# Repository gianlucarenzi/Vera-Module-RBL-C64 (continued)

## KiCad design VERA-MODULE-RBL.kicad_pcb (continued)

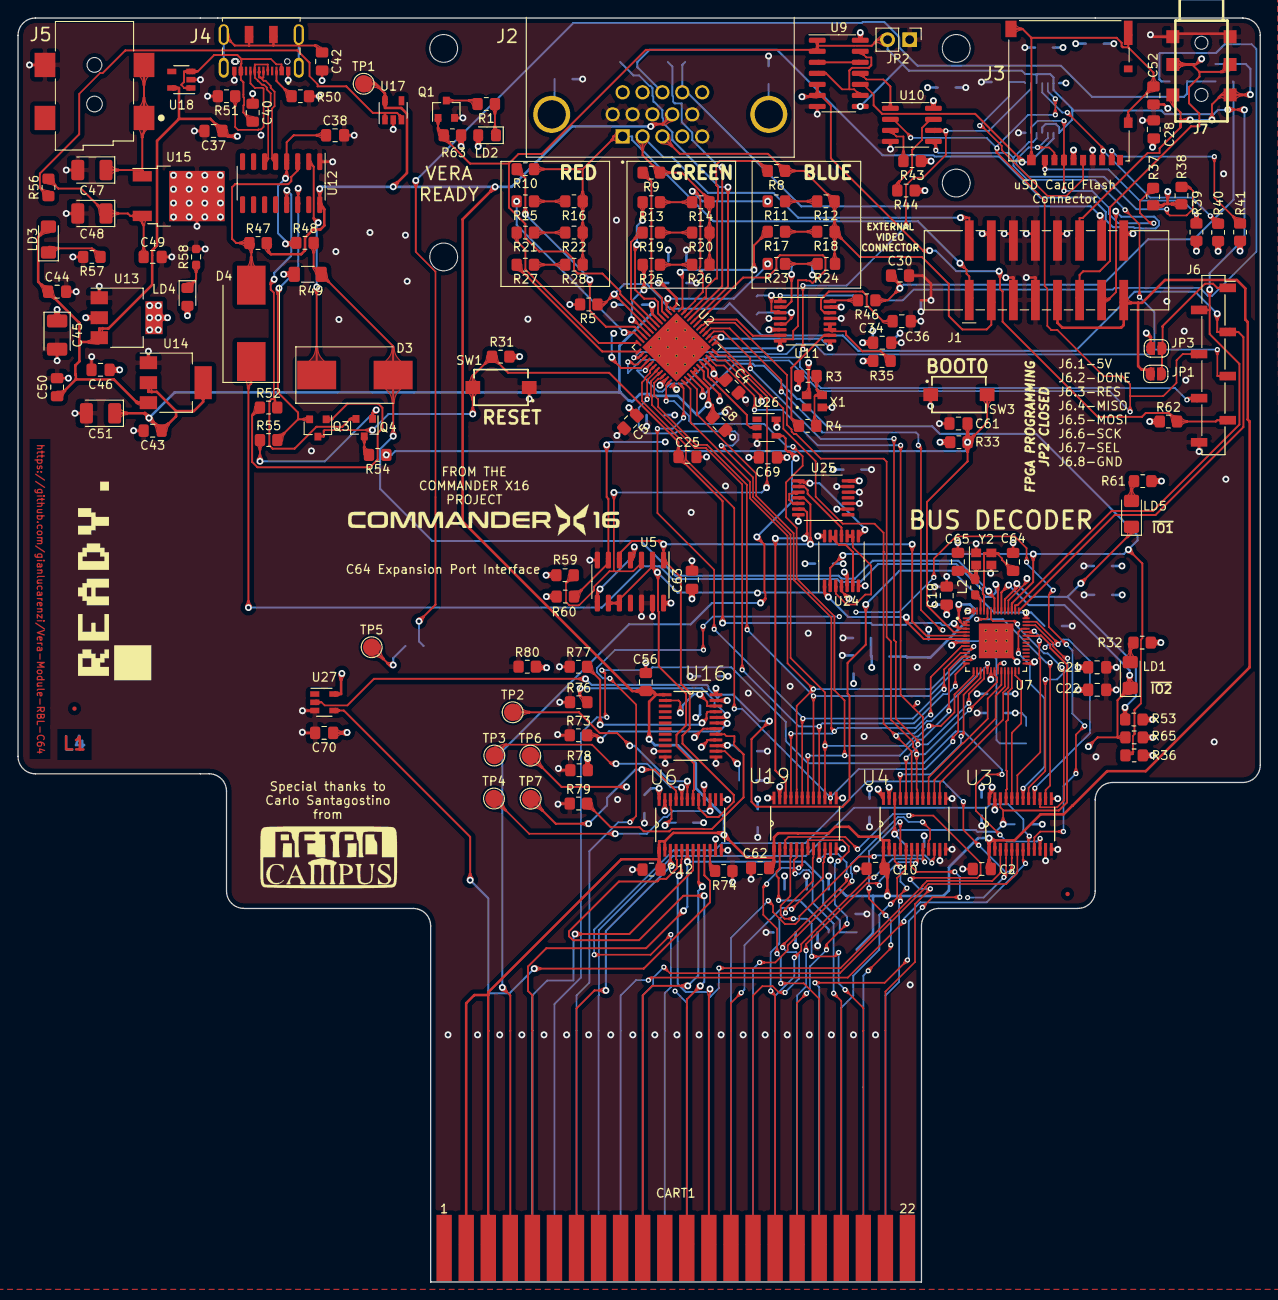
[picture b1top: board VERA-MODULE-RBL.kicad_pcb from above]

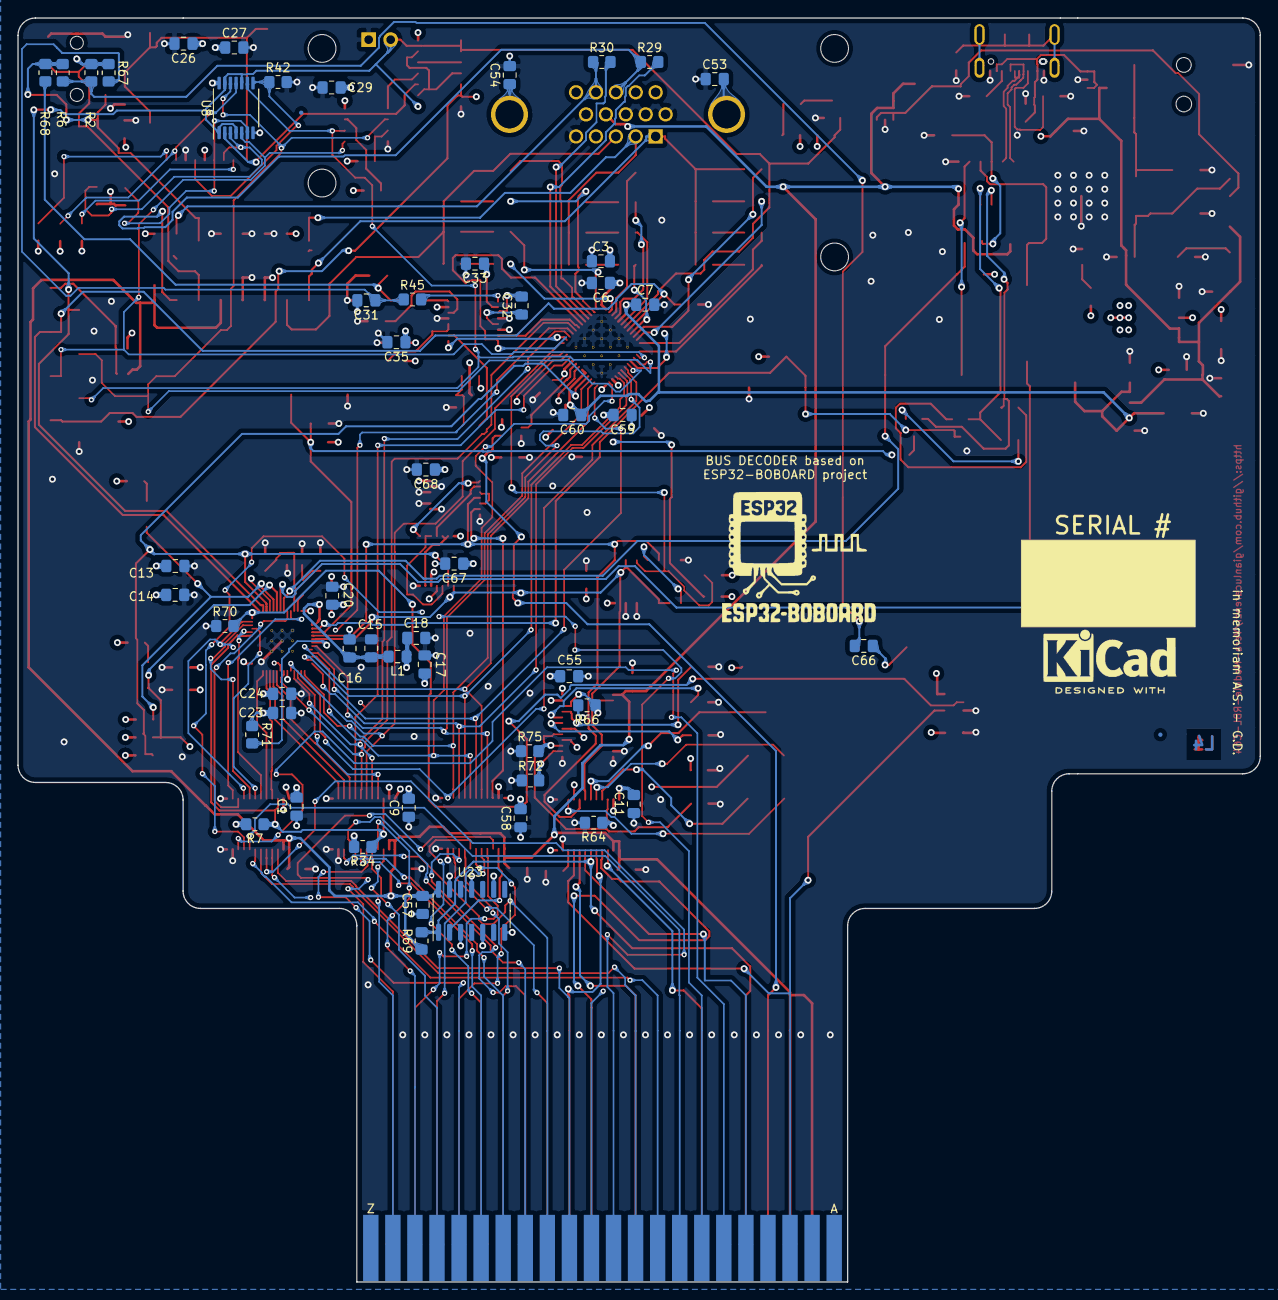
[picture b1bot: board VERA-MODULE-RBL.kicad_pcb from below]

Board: 4 copper layers, 143.0 x 145.5 mm, 219 parts (57 on the bottom side), 193 nets.

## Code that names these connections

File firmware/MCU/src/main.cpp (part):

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 * =========================================================================== */

/* --- Bank 0 Signals (GPIO 0-31) --- */
#define PIN_PHI2        1    /* CPU Clock Phase 2 (Pin 6) */
#define PIN_RW          2    /* Read/Write, High = Read (Pin 7) */

/* D0-D7: GPIO 4 to 11 (Pins 9-16, contiguous in Bank 0): D0 = GPIO 4 */
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#define PIN_A11         34   /* Address Bit 11 (Pin 39) */
#define PIN_A12         35   /* Address Bit 12 (Pin 40) */
#define PIN_A13         36   /* Address Bit 13 (Pin 41) */
#define PIN_ARESET      37   /* C64 /RESET via U27 open-drain, net ~C64_RESET, pull-down R70 (Pin 42) */
#define PIN_CRESET      38   /* Vera Chip Reset Output (Pin 43) */
#define PIN_CDONE       39   /* Vera Programmed Status Input (Pin 44) */
#define PIN_DEV_SEL_N   40   /* Vera Chip Select Output (Pin 45, active LOW) */
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 * code executes.  The levels must be valid when CHIP_PU rises and for
 * t_H = 3 ms after it (datasheet v2.2, §3, Table 3-2).
 *
 * GPIO0  —  Pin  5  |  Boot mode selection  |  Internal weak PULL-UP 45 kΩ
 *   Net BOOT0: R33 4.7 kΩ pull-up, BOOT button SW3, C61 100 nF, and R54 -> Q4
 *   (auto-reset from the programmer).  Not wired to any C64 signal.
 *   CHIP_PU has R31 4.7 kΩ + C25 1 µF (4.7 ms) against 0.47 ms on GPIO0, so
 *   GPIO0 is already HIGH when the reset is released.
 *   Sampled value: HIGH → SPI boot from embedded flash.  LOW (SW3 or Q4)
 *   → joint download boot, which also needs GPIO46 LOW (see below).
 *
 * GPIO3  —  Pin  8  |  JTAG signal source   |  NO internal pull
 *   Not used by the firmware.  R71 10 kΩ pull-up to 3V3 fixes it HIGH, as the
 *   datasheet requires (§3.4: no internal pull, must not be left floating).
 *   Table 3-5: with the default eFuses GPIO3 is ignored and JTAG goes to the
 *   USB Serial/JTAG Controller; HIGH keeps that choice even if
 *   EFUSE_STRAP_JTAG_SEL is burned, so GPIO39-42 never become JTAG pins.
 *
 * GPIO45 —  Pin 51  |  VDD_SPI voltage      |  Internal weak PULL-DOWN 45 kΩ
 * GPIO46 —  Pin 52  |  ROM messages / download mode | Internal weak PULL-DOWN 45 kΩ
 *   A14 and A15, from the expansion port through U3 (74LVC4245).  The port
 *   address lines are always driven: by the 6510 (which keeps driving them
 *   while in reset) or, during PHI1 and VIC-II DMA, by the VIC-II and the
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 *   PIN_ABUS_OE_N (GPIO47) drives ~OE of U3 and U4, and R7/R34 (10 kΩ to 3V3)
 *   hold it HIGH while the ESP32 is in reset (GPIO47 has no pull and no
 *   power-up glitch).  With U3 disabled its outputs are high-Z and the
 *   internal pull-downs read GPIO45 = GPIO46 = LOW at every chip reset:
 *     GPIO45 LOW → VDD_SPI = 3.3 V from VDD3P3_RTC (Table 3-4), the voltage
 *                  of the FN8 in-package flash (HIGH = 1.8 V: no boot);
 *     GPIO46 LOW → ROM messages suppressed; together with GPIO0 LOW it gives
 *                  the joint download boot (GPIO0 LOW + GPIO46 HIGH is
 *                  invalid), so flashing works with the C64 running.
 *   setup() drives PIN_ABUS_OE_N LOW long after the 3 ms hold time; until
 *   then A0-A15 read as LOW or floating: the bus loop starts only afterwards.
 *   Disabling U4 as well also avoids driving GPIO12-19 against U4 during
 *   their power-up glitches (Table 2-2).
 */

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 * (ee.get_gpio_in / ee.wr_mask_gpio_out bypass the APB bus: ~1 cycle).
 *
 * Input channels  (bit index in cpu_ll_read_dedic_gpio_in() result):
 *   Ch 0 = PHI2 (GPIO 1), Ch 1 = R/W (GPIO 2), Ch 2 = /IO1 (GPIO 41),
 *   Ch 3 = /IO2 (GPIO 42)
 *   The GPIO matrix feeds the dedicated inputs without taking the pins away:
 *   the same signals stay visible in GPIO.in / GPIO.in1.
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}

/*
 * PHI2 edge waits: one ee.get_gpio_in and one bit branch per sample
 * (3 cycles), the shortest polling loop.
 */
static inline __attribute__((always_inline)) void wait_phi2_high(void)
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     * Input  bundle: [PHI2, R/W, /IO1, /IO2]  → input  ch 0-3
     * Output bundle: [DEV_SEL_N]              → output ch 0
     */
    static const int dedic_in_pins[]  = { PIN_PHI2, PIN_RW, PIN_IO1_N, PIN_IO2_N };
    static const int dedic_out_pins[] = { PIN_DEV_SEL_N };
    dedic_gpio_bundle_handle_t dedic_in_bundle, dedic_out_bundle;
    const dedic_gpio_bundle_config_t in_cfg =
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         *   2. one APB read of GPIO.in (A0-A7; no memw: the last store, the
         *      bus release, left in the previous PHI1);
         *   3. /IO2: c = io2_cur[A0-A7], DEV_SEL_N for this cycle with one
         *      ee.wr_mask_gpio_out (the VERA strobes are gated by PHI2 in
         *      hardware);
         *   4. /IO1 read: drive win[A0-A7] at once.  U19 passes it to the C64
         *      because /IO1 enables it (hardware gating).
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        {
            /* VERA drives the bus: sample it just before PHI2 falls. */
            uint32_t last = lo, now;
            while ((now = GPIO.in) & (1UL << PIN_PHI2))
                last = now;
            log_send(EVT_REG, (uint8_t)off8, decode_data(last), 0x00u);
        }
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    cfg.mode         = GPIO_MODE_INPUT;

    /* Bank 0 inputs: PHI2, RW, D0-D7, A0-A9 */
    cfg.pin_bit_mask = (1ULL << PIN_PHI2) | (1ULL << PIN_RW) | DBUS_MASK | ABUS_LO_MASK;
    gpio_config(&cfg);

    /* Bank 1 inputs: A10-A15 (wired, not needed for decode), /IO1, /IO2, CDONE */
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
